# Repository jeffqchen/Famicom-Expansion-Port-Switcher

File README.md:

# Famicom Expansion Port Switcher Mod

The expansion ports on the Japanese Famicom consoles have a problem - some western games are incompatible with the controllers connected to this port, due to the fact that this expansion port did not exist on the NES, and therefore was ignored by some devs.

Significant Titles Affected:
- Arkanoid II
- Battletoads
- Dragon's Lair
- Paperboy
- Pinball
- RoboCop 2/3
- Star Force
- Super Mario Bros. USA
- Snake Rattle'n'Roll
- Terminator 1/2
- Tetris (Tengen)
- Zelda II - The Adventure of Link

I created the [FamiCoun](https://github.com/jeffqchen/FamiCoun-Famicom-Front-Expansion-NES-SNES-Adapter) and the [TwinDiamond](https://github.com/jeffqchen/TwinDiamond-Twin-Famicom-Expansion-to-NES-SNES-Controller-Adapter) a few years ago and both suffered from this programming oversight by these devs. So it is only natural for me to take matters into my own hands to fix it.

This switcher mod will enable you to switch the role of the expansion controllers between internal and external. It requires experience in console modding and might not be friendly for everybody. Please keep this in your mind before attempting.

Details are provided in the [Project Wiki](https://github.com/jeffqchen/Famicom-Expansion-Port-Switcher/wiki), separated by console models and motherboard revisions.

-----
## Special Thanks
Voultar (for insisting on a proper logic circuit implementation)
- [Twitter](https://twitter.com/Voultar)

Redherring32 (for providing the board scan of Famicom GPM for reference)
- [Twitter](https://twitter.com/redherring32)
-----

Shield: [![CC BY-SA 4.0][cc-by-sa-shield]][cc-by-sa]

This work is licensed under a
[Creative Commons Attribution-ShareAlike 4.0 International License][cc-by-sa].

[![CC BY-SA 4.0][cc-by-sa-image]][cc-by-sa]

[cc-by-sa]: http://creativecommons.org/licenses/by-sa/4.0/
[cc-by-sa-image]: https://licensebuttons.net/l/by-sa/4.0/88x31.png
[cc-by-sa-shield]: https://img.shields.io/badge/License-CC%20BY--SA%204.0-lightgrey.svg

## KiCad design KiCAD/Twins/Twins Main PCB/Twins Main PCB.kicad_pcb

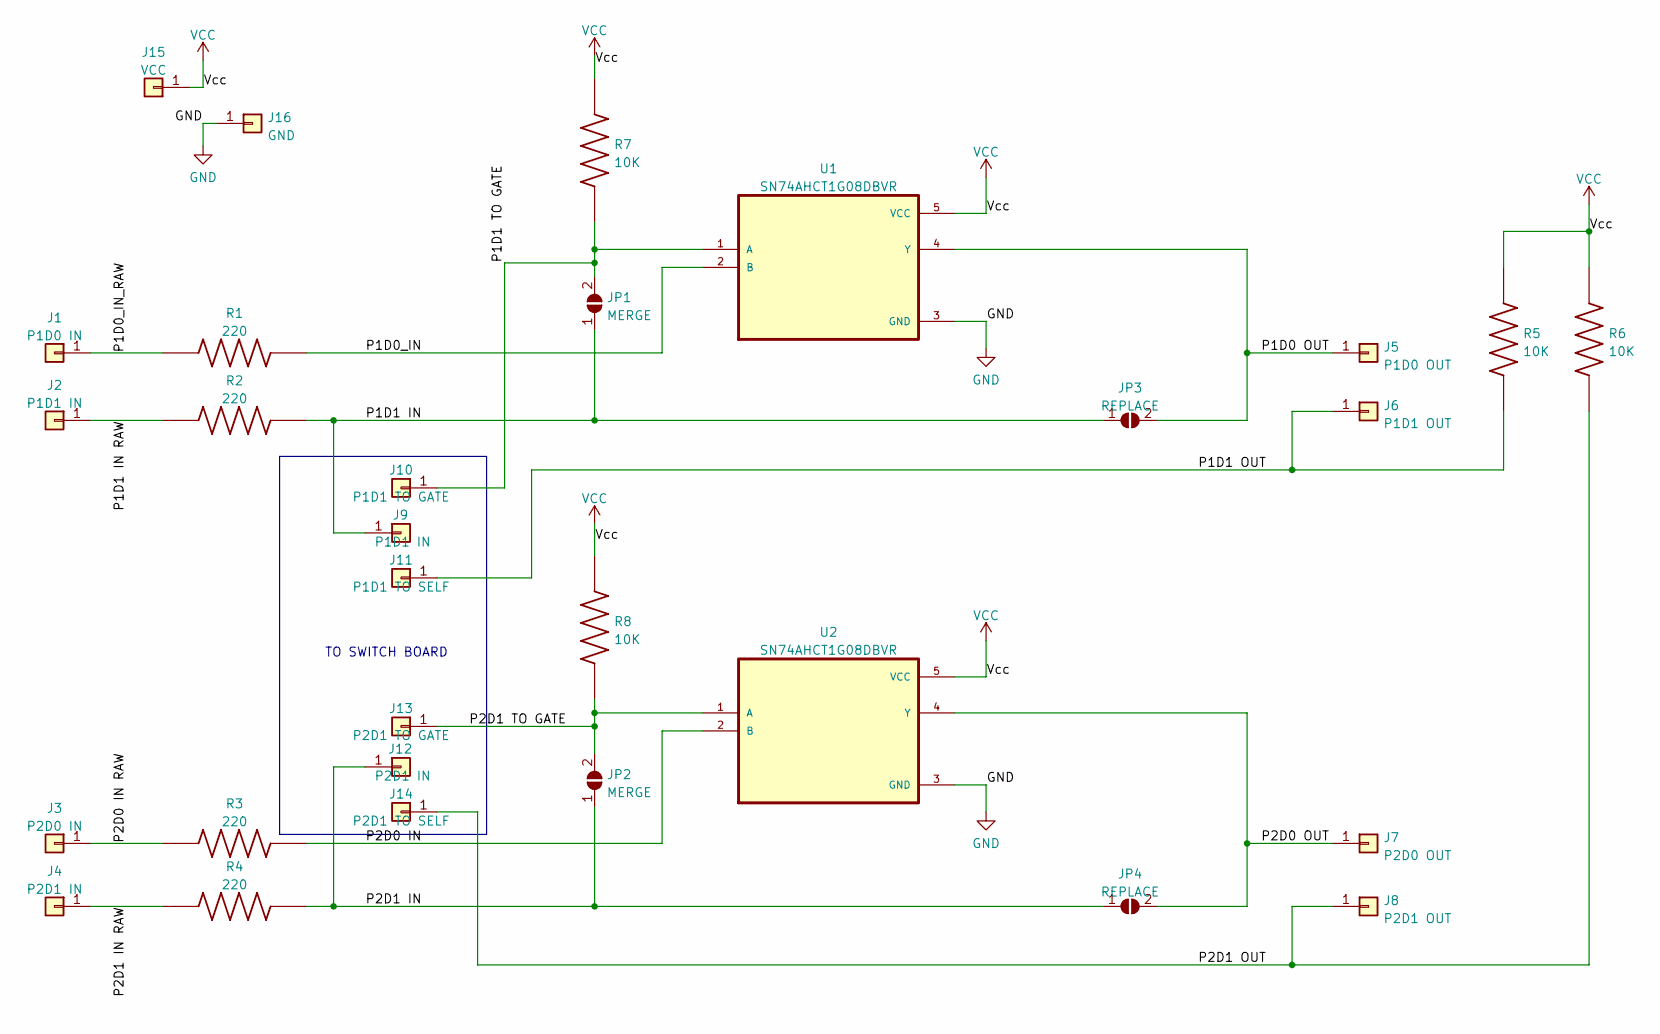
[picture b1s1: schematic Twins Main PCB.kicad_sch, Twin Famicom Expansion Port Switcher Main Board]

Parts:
J1: P1D0 IN; Long Via
J2: P1D1 IN; Long Via
J3: P2D0 IN; Short Via
J4: P2D1 IN; Short Via
J5: P1D0 OUT; Long Via
J6: P1D1 OUT; Long Via
J7: P2D0 OUT; Short Via
J8: P2D1 OUT; Short Via
J9: P1D1 IN; Landing Pad
J10: P1D1 TO GATE; Landing Pad
J11: P1D1 TO SELF; Landing Pad
J12: P2D1 IN; Landing Pad
J13: P2D1 TO GATE; Landing Pad
J14: P2D1 TO SELF; Landing Pad
J15: VCC; Single Pad Pin
J16: GND; Single Pad Pin
JP1, JP2: MERGE; SolderJumper-2_P1.3mm_Open_RoundedPad1.0x1.5mm
JP3, JP4: REPLACE; SolderJumper-2_P1.3mm_Open_RoundedPad1.0x1.5mm
R1, R2, R3, R4: 220; R_0603_1608Metric_Pad0.98x0.95mm_HandSolder
R5, R6, R7, R8: 10K; R_0603_1608Metric_Pad0.98x0.95mm_HandSolder
U1, U2: SN74AHCT1G08DBVR; SOT95P280X145-5N

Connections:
/P1D0 OUT: J5.1, JP3.2 (B), U1.4 (Y)
/P1D0_IN: R1.2, U1.2 (B)
/P1D0_IN_RAW: J1.1, R1.1
/P1D1 IN: J9.1, JP1.1 (A), JP3.1 (A), R2.2
/P1D1 IN RAW: J2.1, R2.1
/P1D1 OUT: J6.1, J11.1, R5.1
/P1D1 TO GATE: J10.1, JP1.2 (B), R7.1, U1.1 (A)
/P2D0 IN: R3.2, U2.2 (B)
/P2D0 IN RAW: J3.1, R3.1
/P2D0 OUT: J7.1, JP4.2 (B), U2.4 (Y)
/P2D1 IN: J12.1, JP2.1 (A), JP4.1 (A), R4.2
/P2D1 IN RAW: J4.1, R4.1
/P2D1 OUT: J8.1, J14.1, R6.1
/P2D1 TO GATE: J13.1, JP2.2 (B), R8.1, U2.1 (A)
GND: J16.1, U1.3 (GND), U2.3 (GND); also elsewhere on the board
VCC: J15.1, R5.2, R6.2, R7.2, R8.2, U1.5 (VCC), U2.5 (VCC); also elsewhere on the board

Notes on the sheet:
TO SWITCH BOARD

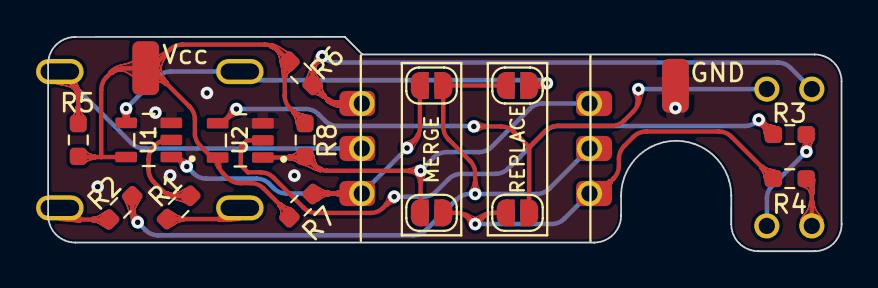
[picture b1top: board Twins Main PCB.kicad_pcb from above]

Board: 2 copper layers, 44.1 x 11.9 mm, 30 parts (0 on the bottom side), 16 nets.

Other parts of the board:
GND: GND; Single Pad Pin
Vcc: VCC; Single Pad Pin

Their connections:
GND: GND.1; also elsewhere on the board
VCC: Vcc.1; also elsewhere on the board

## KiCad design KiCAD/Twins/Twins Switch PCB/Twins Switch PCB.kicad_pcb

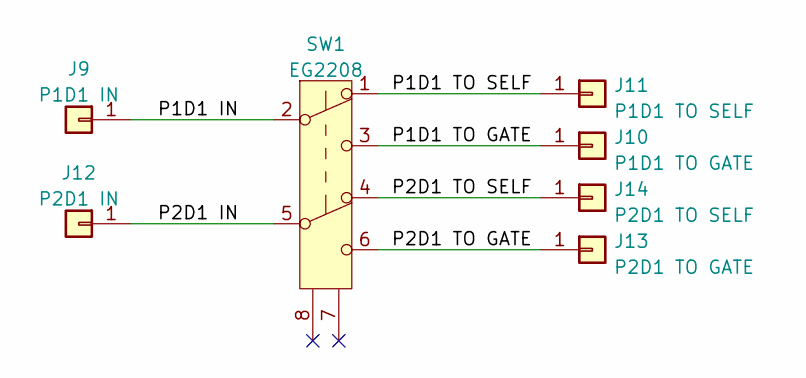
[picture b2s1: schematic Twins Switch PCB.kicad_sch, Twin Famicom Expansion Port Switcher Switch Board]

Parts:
J9: P1D1 IN; Short Via
J10: P1D1 TO GATE; Short Via
J11: P1D1 TO SELF; Short Via
J12: P2D1 IN; Short Via
J13: P2D1 TO GATE; Short Via
J14: P2D1 TO SELF; Short Via
SW1: EG2208; EG2208_DPDT_Switch

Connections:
/P1D1 IN: J9.1, SW1.2 (B)
/P1D1 TO GATE: J10.1, SW1.3 (C)
/P1D1 TO SELF: J11.1, SW1.1 (A)
/P2D1 IN: J12.1, SW1.5 (B)
/P2D1 TO GATE: J13.1, SW1.6 (C)
/P2D1 TO SELF: J14.1, SW1.4 (A)

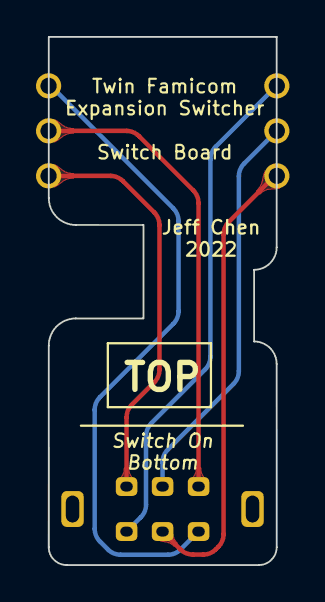
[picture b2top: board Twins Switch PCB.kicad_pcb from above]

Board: 2 copper layers, 12.7 x 29.3 mm, 7 parts (1 on the bottom side), 6 nets.

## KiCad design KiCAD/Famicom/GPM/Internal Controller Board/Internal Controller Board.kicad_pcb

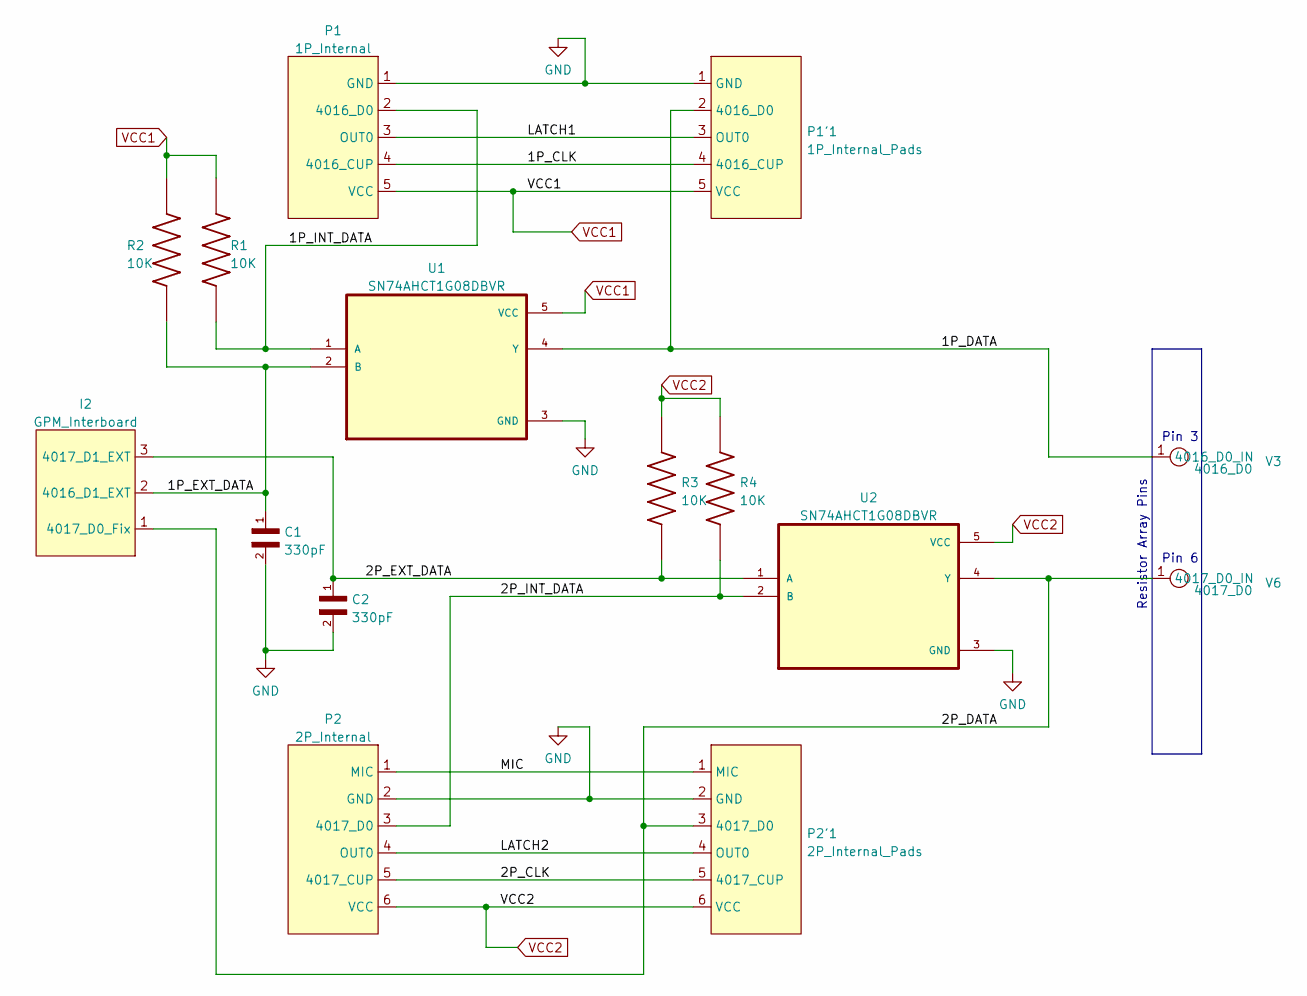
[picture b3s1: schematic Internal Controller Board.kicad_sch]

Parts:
C1, C2: 330pF; C_0603_1608Metric_Pad1.08x0.95mm_HandSolder
I2: GPM_Interboard; GPM Interboard
P1: 1P_Internal; 1P Internal
P1'1: 1P_Internal_Pads; 1P Internal Pads
P2: 2P_Internal; 2P Internal
P2'1: 2P_Internal_Pads; 2P Internal Pads
R1, R2, R3, R4: 10K; R_0603_1608Metric_Pad0.98x0.95mm_HandSolder
U1, U2: SN74AHCT1G08DBVR; SOT95P280X145-5N
V3: 4016_D0; Single Pad Pin
V6: 4017_D0; Single Pad Pin

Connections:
/1P_CLK: P1.4 (4016_CUP), P1'1.4 (4016_CUP)
/1P_DATA: P1'1.2 (4016_D0), U1.4 (Y), V3.1 (4016_D0_IN)
/1P_EXT_DATA: C1.1, I2.2 (4016_D1_EXT), R2.1, U1.2 (B)
/1P_INT_DATA: P1.2 (4016_D0), R1.1, U1.1 (A)
/2P_CLK: P2.5 (4017_CUP), P2'1.5 (4017_CUP)
/2P_DATA: I2.1 (4017_D0_Fix), P2'1.3 (4017_D0), U2.4 (Y), V6.1 (4017_D0_IN)
/2P_EXT_DATA: C2.1, I2.3 (4017_D1_EXT), R3.1, U2.1 (A)
/2P_INT_DATA: P2.3 (4017_D0), R4.1, U2.2 (B)
/LATCH1: P1.3 (OUT0), P1'1.3 (OUT0)
/LATCH2: P2.4 (OUT0), P2'1.4 (OUT0)
/MIC: P2.1 (MIC), P2'1.1 (MIC)
GND: C1.2, C2.2, P1.1 (GND), P1'1.1 (GND), P2.2 (GND), P2'1.2 (GND), U1.3 (GND), U2.3 (GND)
VCC1: P1.5 (VCC), P1'1.5 (VCC), R1.2, R2.2, U1.5 (VCC)
VCC2: P2.6 (VCC), P2'1.6 (VCC), R3.2, R4.2, U2.5 (VCC)

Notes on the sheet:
Pin 3
Pin 6
Resistor Array Pins

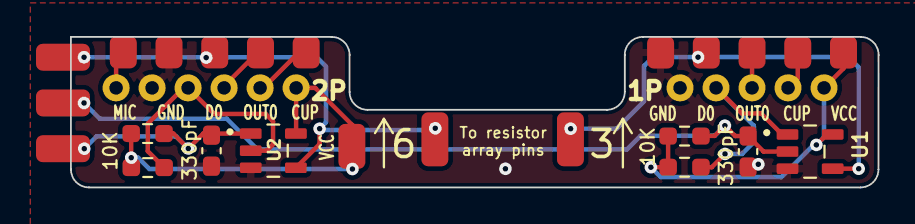
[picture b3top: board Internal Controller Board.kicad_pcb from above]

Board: 2 copper layers, 44.9 x 8.4 mm, 15 parts (0 on the bottom side), 14 nets.

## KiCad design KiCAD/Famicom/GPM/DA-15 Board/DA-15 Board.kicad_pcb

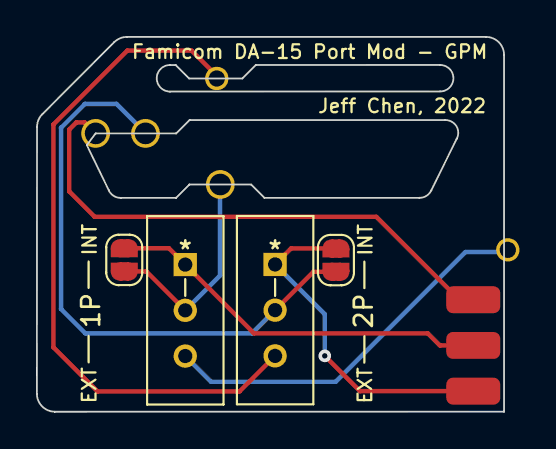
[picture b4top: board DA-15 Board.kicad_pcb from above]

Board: 2 copper layers, 26.0 x 20.8 mm, 8 parts (0 on the bottom side), 7 nets.

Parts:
I1: GPM_Interboard; GPM Interboard
JP1, JP2: SolderJumper_2_Open; SolderJumper-2_P1.3mm_Open_RoundedPad1.0x1.5mm
P1: DA-15 Port; DA-15 Alternate
SW1, SW2: SS12SDP2_NKK; SS12SDP2
V1: 4016_D1; Single Via Pin
V2: 4017_D1; Single Via Pin

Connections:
/4016_D1: SW1.3, V1.1 (4016_D1_IN)
/4016_D1_EXT: JP1.2 (B), P1.13 (4016_D1), SW1.2
/4016_D1_INT: I1.2 (4016_D1_EXT), JP1.1 (A), SW1.1
/4017_D1: SW2.3, V2.1 (4017_D1_IN)
/4017_D1_EXT: JP2.2 (B), P1.7 (4017_D1), SW2.2
/4017_D1_INT: I1.3 (4017_D1_EXT), JP2.1 (A), SW2.1
/TO_EXT_4017_D0: I1.1 (4017_D0_Fix), P1.8 (4017_D0)

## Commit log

2022-10-02 Update pics and readme
2022-10-03 Add pics
2022-12-01 Twins Mod Initial Upload
2022-12-01 Add indicators for resistors to remove

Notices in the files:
parts and their libraries:
Copyright 2021 Accelerated Designs. All rights reserved.
